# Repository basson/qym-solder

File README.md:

# qym-solder
QymSolder - Soldering station  three in one - hakko t12, hot air gun, d909/898D or analog.

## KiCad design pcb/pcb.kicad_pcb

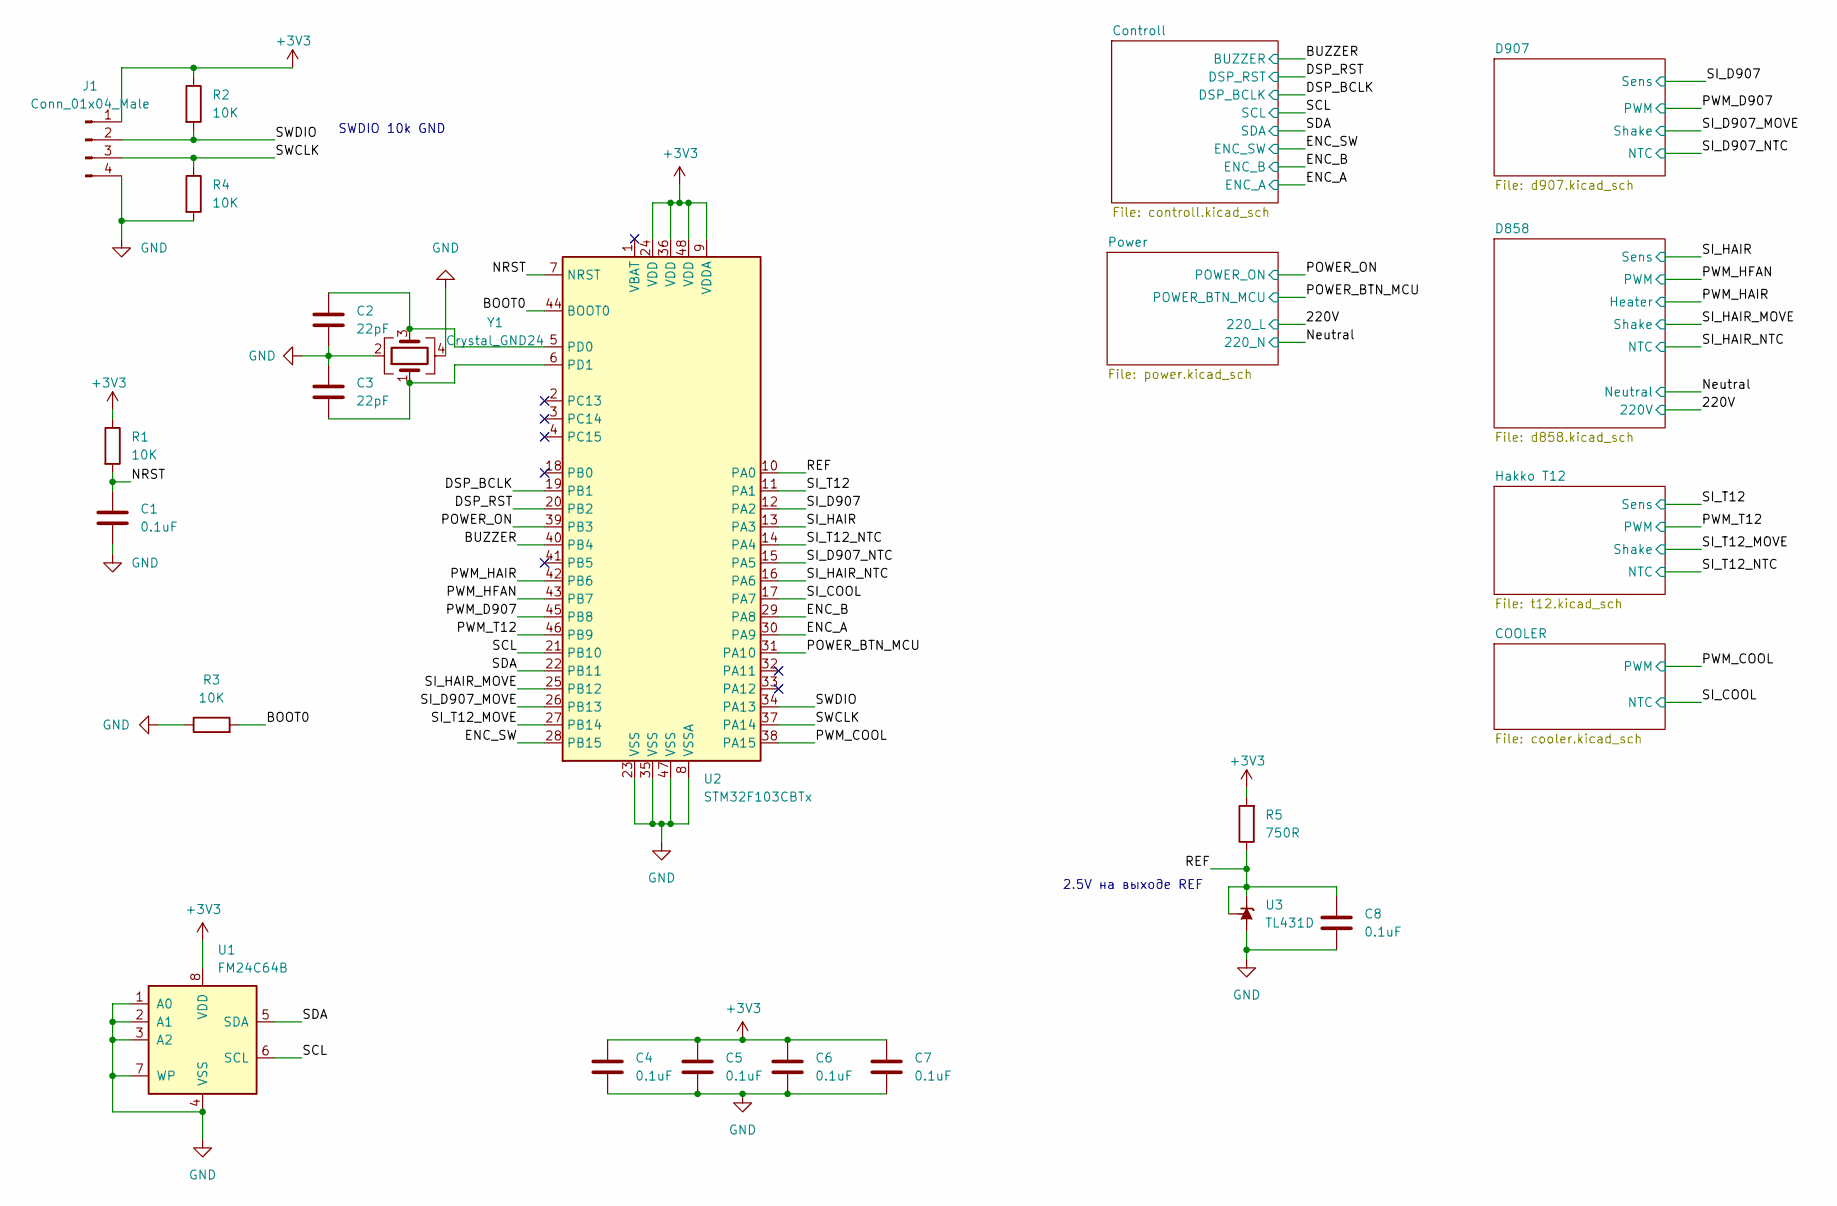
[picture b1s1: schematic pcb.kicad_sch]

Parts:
C1, C4, C5, C6, C7, C8: 0.1uF; C_1206_3216Metric_Pad1.33x1.80mm_HandSolder
C2, C3: 22pF; C_1206_3216Metric_Pad1.33x1.80mm_HandSolder
J1: Conn_01x04_Male; PinSocket_1x04_P2.54mm_Vertical
R1, R2, R3, R4: 10K; R_1206_3216Metric_Pad1.30x1.75mm_HandSolder
R5: 750R; R_1206_3216Metric_Pad1.30x1.75mm_HandSolder
U1: FM24C64B; SOIC-8_3.9x4.9mm_P1.27mm
U2: STM32F103CBTx; LQFP-48_7x7mm_P0.5mm
U3: TL431D; SOIC-8_3.9x4.9mm_P1.27mm
Y1: Crystal_GND24; Crystal_SMD_5032-4Pin_5.0x3.2mm

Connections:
+3V3: C4.1, C5.1, C6.1, C7.1, J1.1, R1.1, R2.1, R5.2, U1.8 (VDD), U2.9 (VDDA), U2.24 (VDD), U2.36 (VDD), U2.48 (VDD); also elsewhere on the board
/BOOT0: R3.2, U2.44 (BOOT0)
/BUZZER: U2.40 (PB4); also elsewhere on the board
/DSP_BCLK: U2.19 (PB1); also elsewhere on the board
/DSP_RST: U2.20 (PB2); also elsewhere on the board
/ENC_A: U2.30 (PA9); also elsewhere on the board
/ENC_B: U2.29 (PA8); also elsewhere on the board
/ENC_SW: U2.28 (PB15); also elsewhere on the board
/NRST: C1.2, R1.2, U2.7 (NRST)
/POWER_BTN_MCU: U2.31 (PA10); also elsewhere on the board
/POWER_ON: U2.39 (PB3); also elsewhere on the board
/PWM_COOL: U2.38 (PA15); also elsewhere on the board
/PWM_D907: U2.45 (PB8); also elsewhere on the board
/PWM_HAIR: U2.42 (PB6); also elsewhere on the board
/PWM_HFAN: U2.43 (PB7); also elsewhere on the board
/PWM_T12: U2.46 (PB9); also elsewhere on the board
/REF: C8.1, R5.1, U2.10 (PA0), U3.1 (K), U3.8 (REF)
/SCL: U1.6 (SCL), U2.21 (PB10); also elsewhere on the board
/SDA: U1.5 (SDA), U2.22 (PB11); also elsewhere on the board
/SI_COOL: U2.17 (PA7); also elsewhere on the board
/SI_D907: U2.12 (PA2); also elsewhere on the board
/SI_D907_MOVE: U2.26 (PB13); also elsewhere on the board
/SI_D907_NTC: U2.15 (PA5); also elsewhere on the board
/SI_HAIR: U2.13 (PA3); also elsewhere on the board
/SI_HAIR_MOVE: U2.25 (PB12); also elsewhere on the board
/SI_HAIR_NTC: U2.16 (PA6); also elsewhere on the board
/SI_T12: U2.11 (PA1); also elsewhere on the board
/SI_T12_MOVE: U2.27 (PB14); also elsewhere on the board
/SI_T12_NTC: U2.14 (PA4); also elsewhere on the board
/SWCLK: J1.3, R4.1, U2.37 (PA14)
/SWDIO: J1.2, R2.2, U2.34 (PA13)
GND: C1.1, C2.1, C3.2, C4.2, C5.2, C6.2, C7.2, C8.2, J1.4, R3.1, R4.2, U1.1 (A0), U1.2 (A1), U1.3 (A2), U1.4 (VSS), U1.7 (WP), U2.8 (VSSA), U2.23 (VSS), U2.35 (VSS), U2.47 (VSS), U3.2 (A), U3.3 (A), U3.6 (A), U3.7 (A), Y1.2, Y1.4; also elsewhere on the board
unnamed: C2.2, U2.5 (PD0), Y1.3
unnamed: C3.1, U2.6 (PD1), Y1.1

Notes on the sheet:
2.5V на выходе REF
SWDIO 10k GND

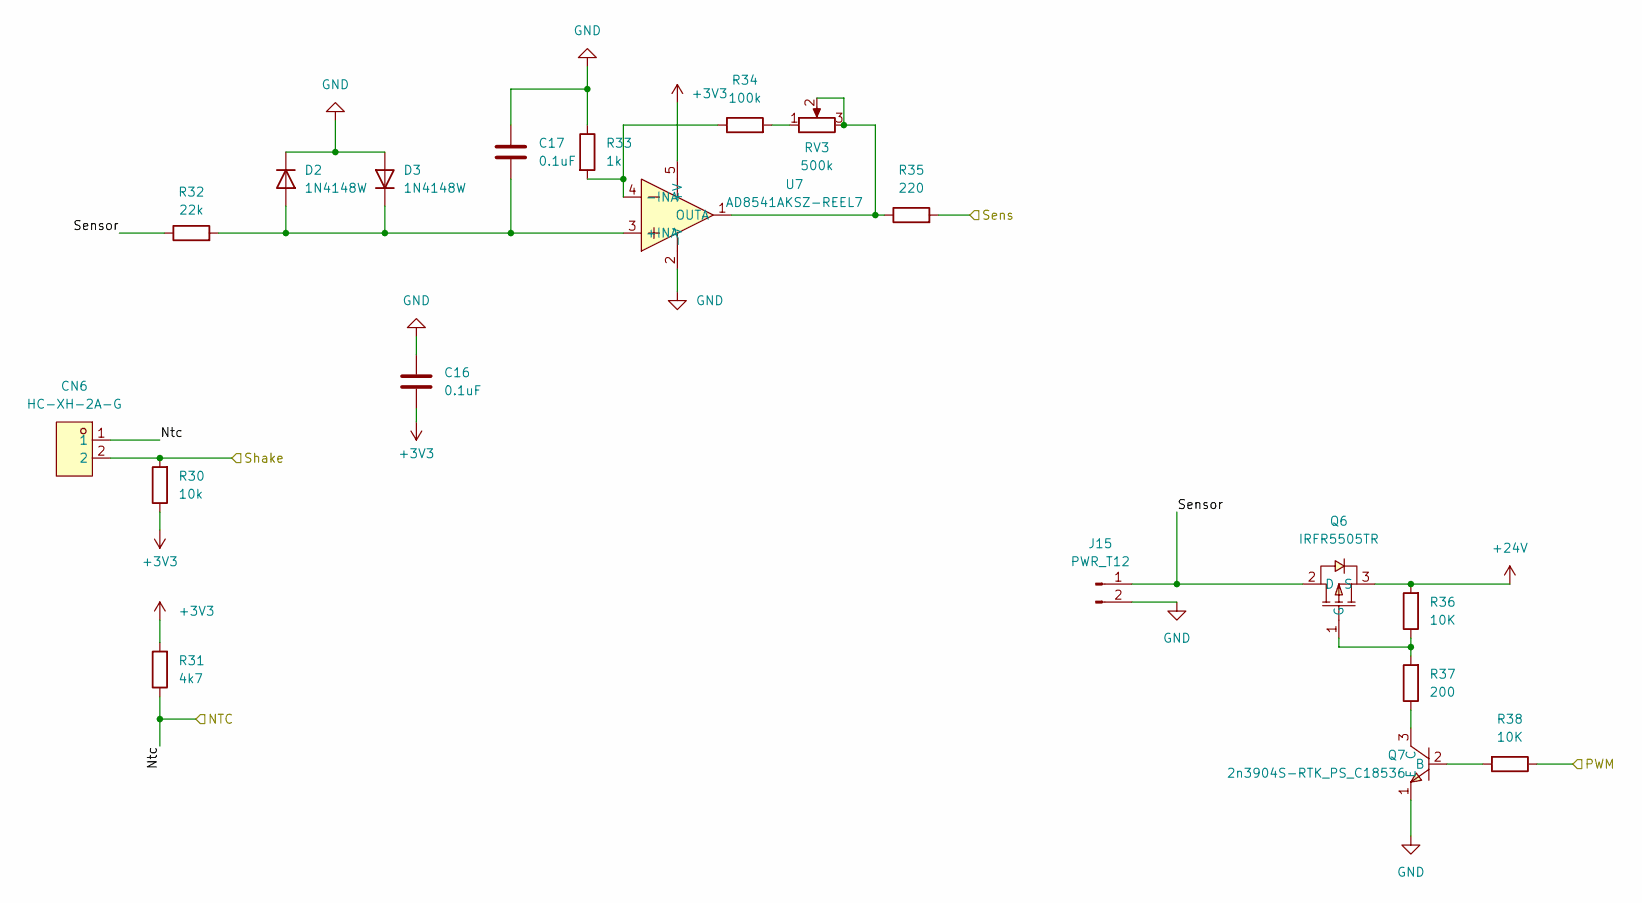
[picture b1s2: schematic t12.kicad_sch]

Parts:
C16, C17: 0.1uF; C_1206_3216Metric_Pad1.33x1.80mm_HandSolder
CN6: HC-XH-2A-G; CONN-TH_2P-P2.50_HC-XH-2A-G; LCSC Part C5341201
D2, D3: 1N4148W; D_SOD-123
J15: PWR_T12; TerminalBlock_Phoenix_MKDS-1,5-2_1x02_P5.00mm_Horizontal
Q6: IRFR5505TR; TO-252-3_L6.5-W5.8-P4.58-BR; LCSC Part C725084
Q7: 2n3904S-RTK_PS_C18536; SOT-23-3_L2.9-W1.3-P1.90-LS2.4-TR; LCSC Part C18536
R30: 10k; R_1206_3216Metric_Pad1.30x1.75mm_HandSolder
R31: 4k7; R_1206_3216Metric_Pad1.30x1.75mm_HandSolder
R32: 22k; R_1206_3216Metric_Pad1.30x1.75mm_HandSolder
R33: 1k; R_1206_3216Metric_Pad1.30x1.75mm_HandSolder
R34: 100k; R_1206_3216Metric_Pad1.30x1.75mm_HandSolder
R35: 220; R_1206_3216Metric_Pad1.30x1.75mm_HandSolder
R36, R38: 10K; R_1206_3216Metric_Pad1.30x1.75mm_HandSolder
R37: 200; R_1206_3216Metric_Pad1.30x1.75mm_HandSolder
RV3: 500k; Potentiometer_Bourns_3296W_Vertical
U7: AD8541AKSZ-REEL7; SOT-23-5; LCSC Part C143907

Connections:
+3V3: C16.2, R30.1, R31.2, U7.5 (+V); also elsewhere on the board
+24V: Q6.3 (S), R36.2; also elsewhere on the board
/Hakko T12/Sensor: J15.1, Q6.2 (D), R32.1
/PWM_T12: R38.1; also elsewhere on the board
/SI_T12: R35.2; also elsewhere on the board
/SI_T12_MOVE: CN6.2, R30.2; also elsewhere on the board
/SI_T12_NTC: CN6.1, R31.1; also elsewhere on the board
GND: C16.1, C17.1, D2.1 (K), D3.2 (A), J15.2, Q7.1 (E), R33.1, U7.2 (-V); also elsewhere on the board
unnamed: C17.2, D2.2 (A), D3.1 (K), R32.2, U7.3 (+INA)
unnamed: Q6.1 (G), R36.1, R37.2
unnamed: Q7.2 (B), R38.2
unnamed: Q7.3 (C), R37.1
unnamed: R34.2, RV3.1
unnamed: R33.2, R34.1, U7.4 (-INA)
unnamed: R35.1, RV3.2, RV3.3, U7.1 (OUTA)

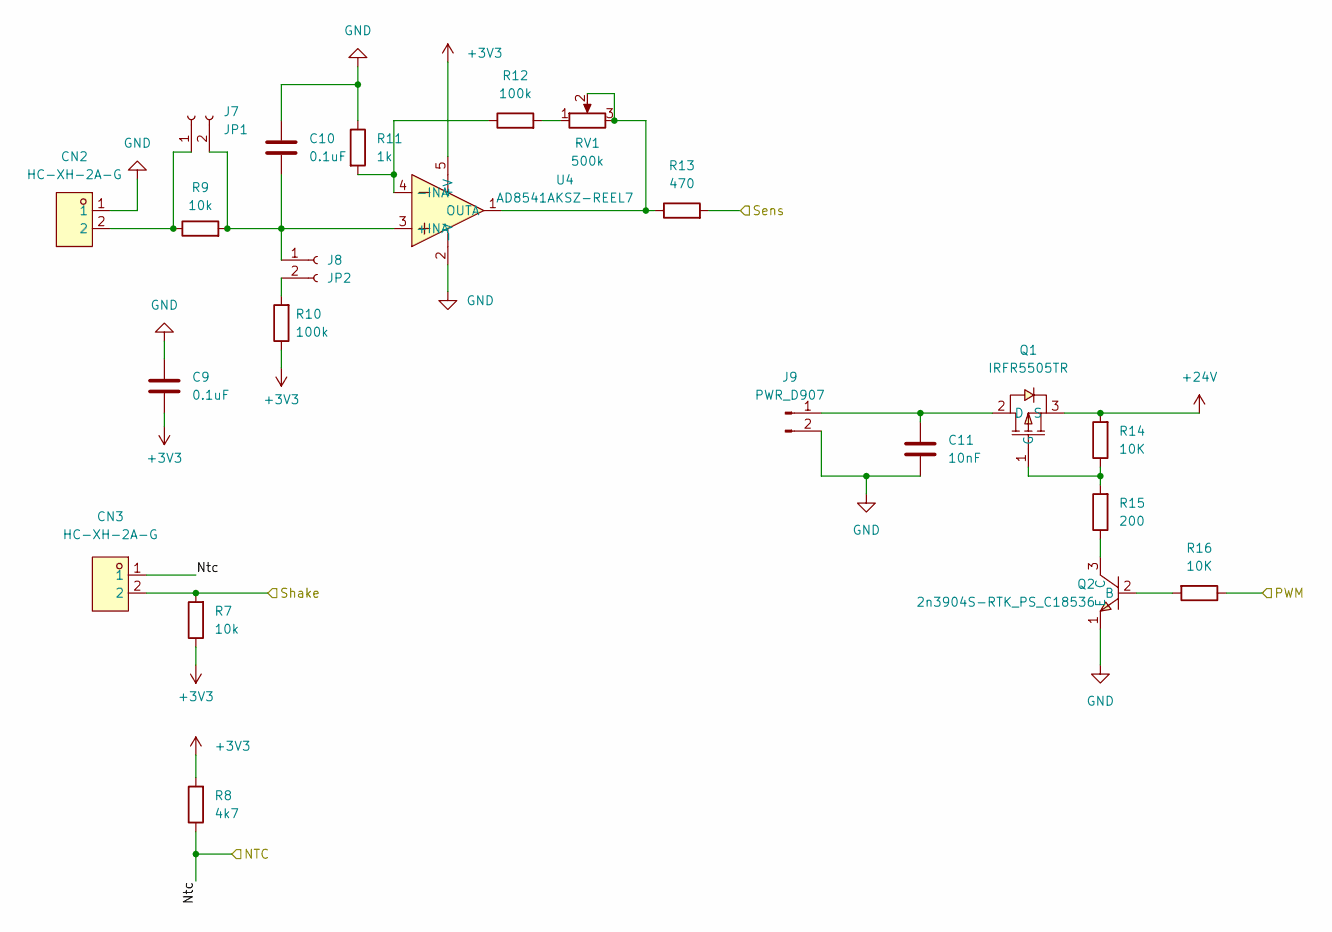
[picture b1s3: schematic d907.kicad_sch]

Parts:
C9, C10: 0.1uF; C_1206_3216Metric_Pad1.33x1.80mm_HandSolder
C11: 10nF; C_1206_3216Metric_Pad1.33x1.80mm_HandSolder
CN2, CN3: HC-XH-2A-G; CONN-TH_2P-P2.50_HC-XH-2A-G; LCSC Part C5341201
J7: JP1; PinSocket_1x02_P2.54mm_Vertical
J8: JP2; PinSocket_1x02_P2.54mm_Vertical
J9: PWR_D907; TerminalBlock_Phoenix_MKDS-1,5-2_1x02_P5.00mm_Horizontal
Q1: IRFR5505TR; TO-252-3_L6.5-W5.8-P4.58-BR; LCSC Part C725084
Q2: 2n3904S-RTK_PS_C18536; SOT-23-3_L2.9-W1.3-P1.90-LS2.4-TR; LCSC Part C18536
R7, R9: 10k; R_1206_3216Metric_Pad1.30x1.75mm_HandSolder
R8: 4k7; R_1206_3216Metric_Pad1.30x1.75mm_HandSolder
R10, R12: 100k; R_1206_3216Metric_Pad1.30x1.75mm_HandSolder
R11: 1k; R_1206_3216Metric_Pad1.30x1.75mm_HandSolder
R13: 470; R_1206_3216Metric_Pad1.30x1.75mm_HandSolder
R14, R16: 10K; R_1206_3216Metric_Pad1.30x1.75mm_HandSolder
R15: 200; R_1206_3216Metric_Pad1.30x1.75mm_HandSolder
RV1: 500k; Potentiometer_Bourns_3296W_Vertical
U4: AD8541AKSZ-REEL7; SOT-23-5; LCSC Part C143907

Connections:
+3V3: C9.2, R7.1, R8.2, R10.1, U4.5 (+V); also elsewhere on the board
+24V: Q1.3 (S), R14.2; also elsewhere on the board
/PWM_D907: R16.1; also elsewhere on the board
/SI_D907: R13.2; also elsewhere on the board
/SI_D907_MOVE: CN3.2, R7.2; also elsewhere on the board
/SI_D907_NTC: CN3.1, R8.1; also elsewhere on the board
GND: C9.1, C10.1, C11.1, CN2.1, J9.2, Q2.1 (E), R11.1, U4.2 (-V); also elsewhere on the board
unnamed: CN2.2, J7.1, R9.1
unnamed: C10.2, J7.2, J8.1, R9.2, U4.3 (+INA)
unnamed: J8.2, R10.2
unnamed: C11.2, J9.1, Q1.2 (D)
unnamed: Q1.1 (G), R14.1, R15.2
unnamed: Q2.2 (B), R16.2
unnamed: Q2.3 (C), R15.1
unnamed: R12.2, RV1.1
unnamed: R11.2, R12.1, U4.4 (-INA)
unnamed: R13.1, RV1.2, RV1.3, U4.1 (OUTA)

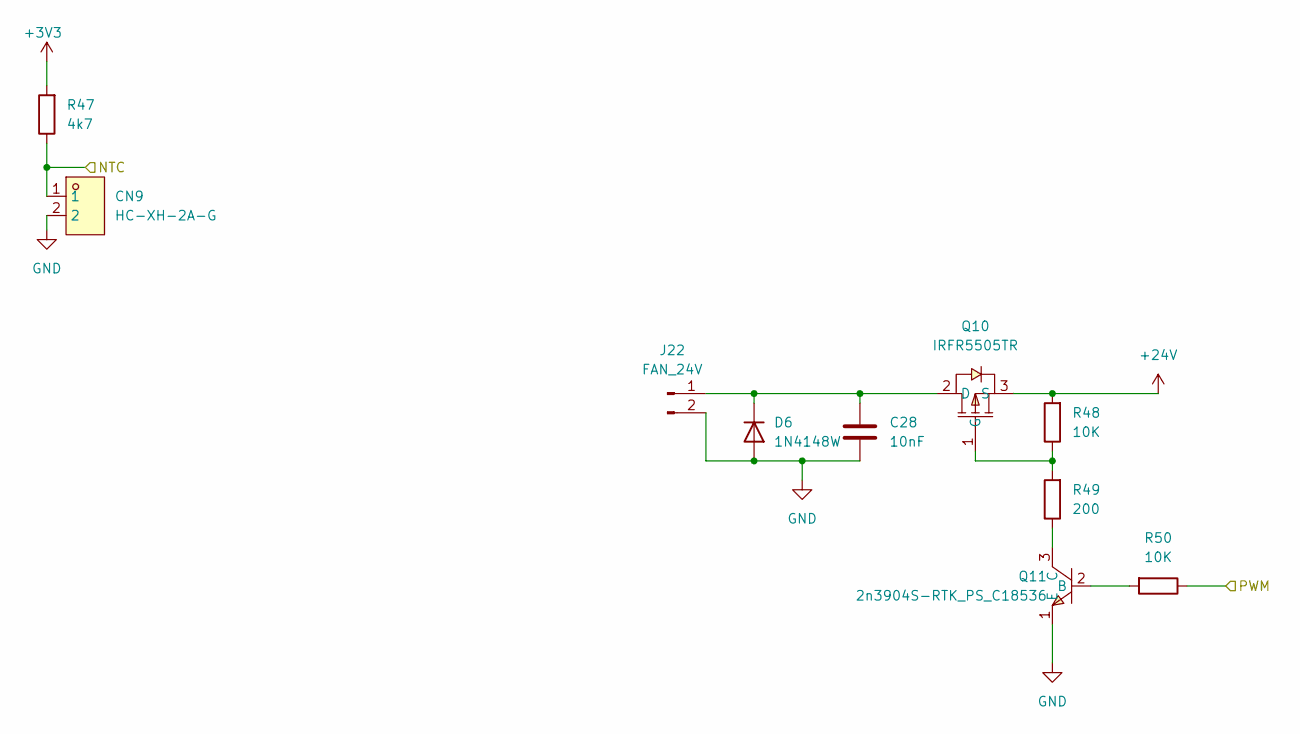
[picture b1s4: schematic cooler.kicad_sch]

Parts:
C28: 10nF; C_1206_3216Metric_Pad1.33x1.80mm_HandSolder
CN9: HC-XH-2A-G; CONN-TH_2P-P2.50_HC-XH-2A-G; LCSC Part C5341201
D6: 1N4148W; D_SOD-123
J22: FAN_24V; TerminalBlock_Phoenix_MKDS-1,5-2_1x02_P5.00mm_Horizontal
Q10: IRFR5505TR; TO-252-3_L6.5-W5.8-P4.58-BR; LCSC Part C725084
Q11: 2n3904S-RTK_PS_C18536; SOT-23-3_L2.9-W1.3-P1.90-LS2.4-TR; LCSC Part C18536
R47: 4k7; R_1206_3216Metric_Pad1.30x1.75mm_HandSolder
R48, R50: 10K; R_1206_3216Metric_Pad1.30x1.75mm_HandSolder
R49: 200; R_1206_3216Metric_Pad1.30x1.75mm_HandSolder

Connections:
+3V3: R47.2; also elsewhere on the board
+24V: Q10.3 (S), R48.2; also elsewhere on the board
/PWM_COOL: R50.1; also elsewhere on the board
/SI_COOL: CN9.1, R47.1; also elsewhere on the board
GND: C28.1, CN9.2, D6.2 (A), J22.2, Q11.1 (E); also elsewhere on the board
unnamed: C28.2, D6.1 (K), J22.1, Q10.2 (D)
unnamed: Q10.1 (G), R48.1, R49.2
unnamed: Q11.2 (B), R50.2
unnamed: Q11.3 (C), R49.1

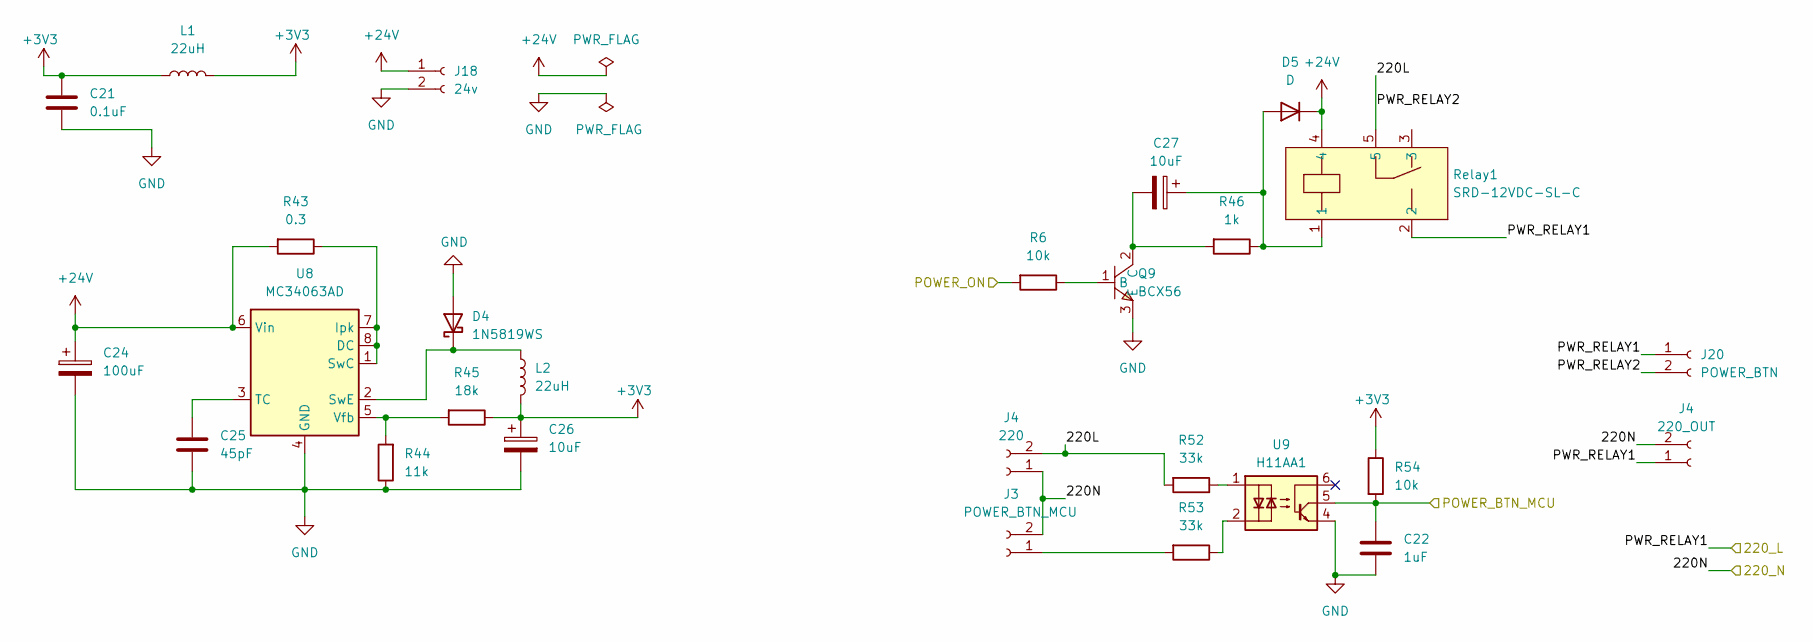
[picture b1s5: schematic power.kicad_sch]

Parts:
C21: 0.1uF; C_1206_3216Metric_Pad1.33x1.80mm_HandSolder
C22: 1uF; C_1206_3216Metric_Pad1.33x1.80mm_HandSolder
C24: 100uF; CP_Radial_D8.0mm_P3.80mm
C25: 45pF; C_1206_3216Metric_Pad1.33x1.80mm_HandSolder
C26, C27: 10uF; CP_Radial_D5.0mm_P2.50mm
D4: 1N5819WS; D_2114_3652Metric_Pad1.85x3.75mm_HandSolder
D5: D; D_SMA_Handsoldering
J3: POWER_BTN_MCU; TerminalBlock_Phoenix_MKDS-1,5-2_1x02_P5.00mm_Horizontal
J4: 220; TerminalBlock_Phoenix_MKDS-1,5-2_1x02_P5.00mm_Horizontal
J18: 24v; TerminalBlock_Phoenix_MKDS-1,5-2_1x02_P5.00mm_Horizontal
J20: POWER_BTN; TerminalBlock_Phoenix_MKDS-1,5-2_1x02_P5.00mm_Horizontal
L1: 22uH; L_1206_3216Metric_Pad1.22x1.90mm_HandSolder
L2: 22uH; L_6.3x6.3_H3
Q9: BCX56; SOT-89-3_L4.5-W2.5-P1.50-LS4.2-BR; LCSC Part C24280
R6, R54: 10k; R_1206_3216Metric_Pad1.30x1.75mm_HandSolder
R43: 0.3; R_1206_3216Metric_Pad1.30x1.75mm_HandSolder
R44: 11k; R_1206_3216Metric_Pad1.30x1.75mm_HandSolder
R45: 18k; R_1206_3216Metric_Pad1.30x1.75mm_HandSolder
R46: 1k; R_1206_3216Metric_Pad1.30x1.75mm_HandSolder
R52, R53: 33k; R_2512_6332Metric_Pad1.40x3.35mm_HandSolder
Relay1: SRD-12VDC-SL-C; RELAY-TH_SRD-XXVDC-XL-C; LCSC Part C30431
U8: MC34063AD; SOIC-8_3.9x4.9mm_P1.27mm
U9: H11AA1; DIP-6_W7.62mm_SMDSocket_SmallPads

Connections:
+3V3: C21.1, C26.1, L1.1, L1.2, L2.2, R45.1, R54.1; also elsewhere on the board
+24V: C24.1, D5.1 (K), J18.1, R43.2, Relay1.4, U8.6 (Vin); also elsewhere on the board
/POWER_BTN_MCU: C22.1, R54.2, U9.5; also elsewhere on the board
/POWER_ON: R6.2; also elsewhere on the board
GND: C21.2, C22.2, C24.2, C25.2, C26.2, D4.2 (A), J18.2, Q9.3 (E), R44.1, U8.4 (GND), U9.4; also elsewhere on the board
unnamed: D4.1 (K), L2.1, U8.2 (SwE)
unnamed: C27.1, D5.2 (A), R46.1, Relay1.1
unnamed: J3.1, R53.2
unnamed: Q9.1 (B), R6.1
unnamed: C27.2, Q9.2 (C), R46.2
unnamed: R52.1, U9.1
unnamed: R53.1, U9.2
unnamed: R43.1, U8.1 (SwC), U8.7 (Ipk), U8.8 (DC)
unnamed: C25.1, U8.3 (TC)
unnamed: R44.2, R45.2, U8.5 (Vfb)

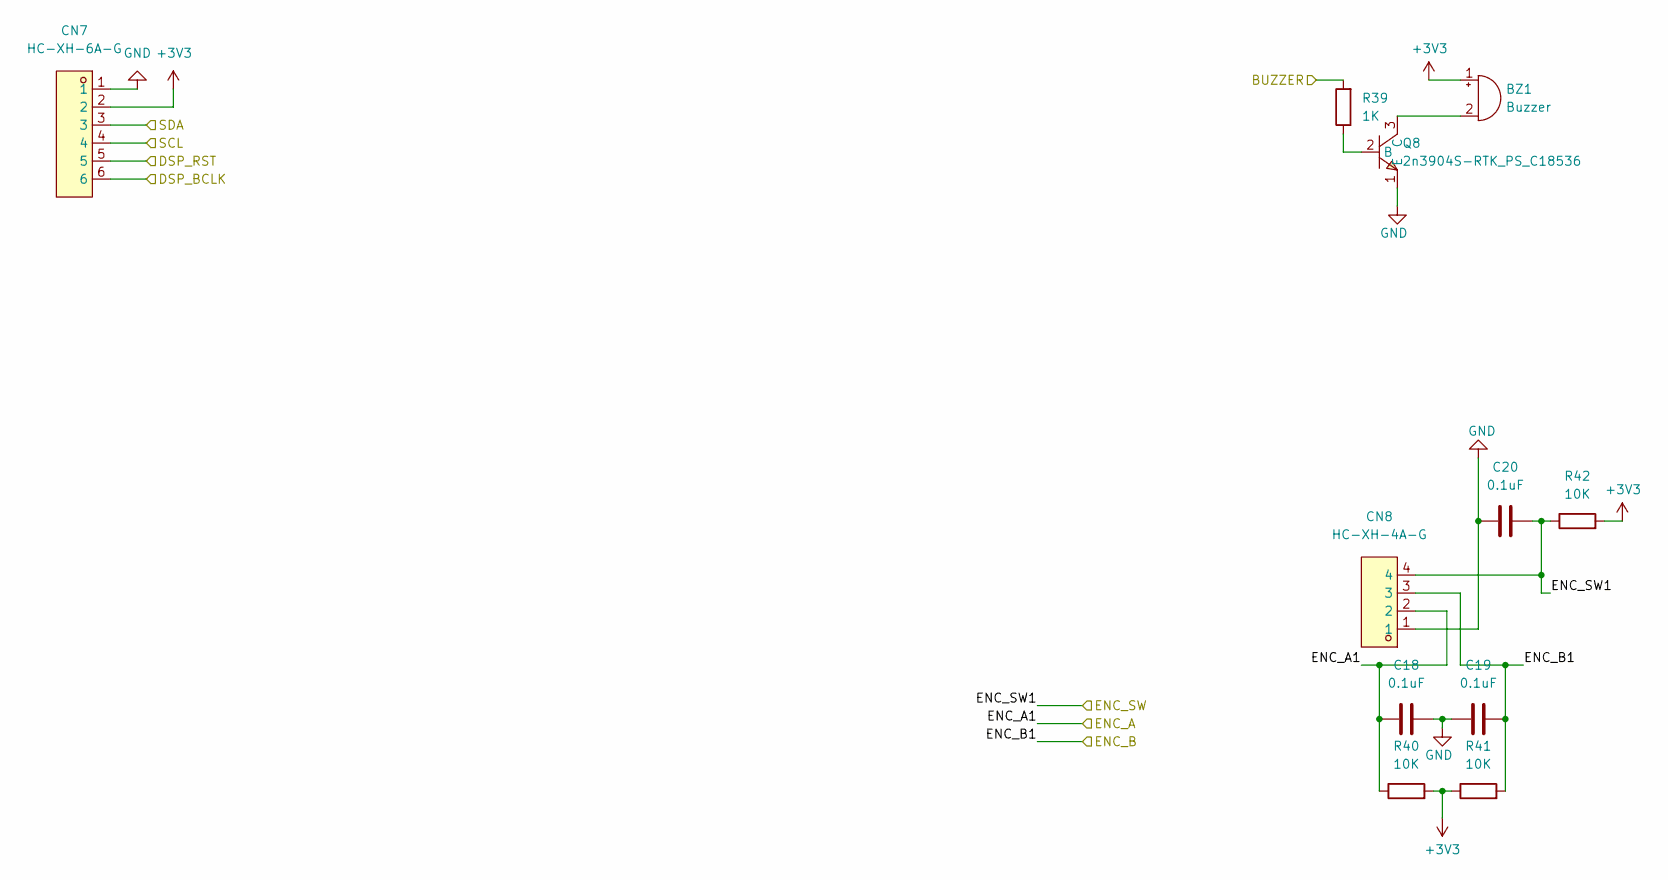
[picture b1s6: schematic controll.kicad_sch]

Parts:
BZ1: Buzzer; Buzzer_12x9.5RM7.6
C18, C19, C20: 0.1uF; C_1206_3216Metric_Pad1.33x1.80mm_HandSolder
CN7: HC-XH-6A-G; CONN-TH_6P-P2.50_HC-XH-6A-G; LCSC Part C5341205
CN8: HC-XH-4A-G; CONN-TH_4P-P2.50_HC-XH-4A-G; LCSC Part C5341203
Q8: 2n3904S-RTK_PS_C18536; SOT-23-3_L2.9-W1.3-P1.90-LS2.4-TR; LCSC Part C18536
R39: 1K; R_1206_3216Metric_Pad1.30x1.75mm_HandSolder
R40, R41, R42: 10K; R_1206_3216Metric_Pad1.30x1.75mm_HandSolder

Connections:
+3V3: BZ1.1 (-), CN7.2, R40.2, R41.1, R42.2; also elsewhere on the board
/BUZZER: R39.2; also elsewhere on the board
/DSP_BCLK: CN7.6; also elsewhere on the board
/DSP_RST: CN7.5; also elsewhere on the board
/ENC_A: C18.1, CN8.2, R40.1; also elsewhere on the board
/ENC_B: C19.2, CN8.3, R41.2; also elsewhere on the board
/ENC_SW: C20.1, CN8.4, R42.1; also elsewhere on the board
/SCL: CN7.4; also elsewhere on the board
/SDA: CN7.3; also elsewhere on the board
GND: C18.2, C19.1, C20.2, CN7.1, CN8.1, Q8.1 (E); also elsewhere on the board
unnamed: BZ1.2 (+), Q8.3 (C)
unnamed: Q8.2 (B), R39.1

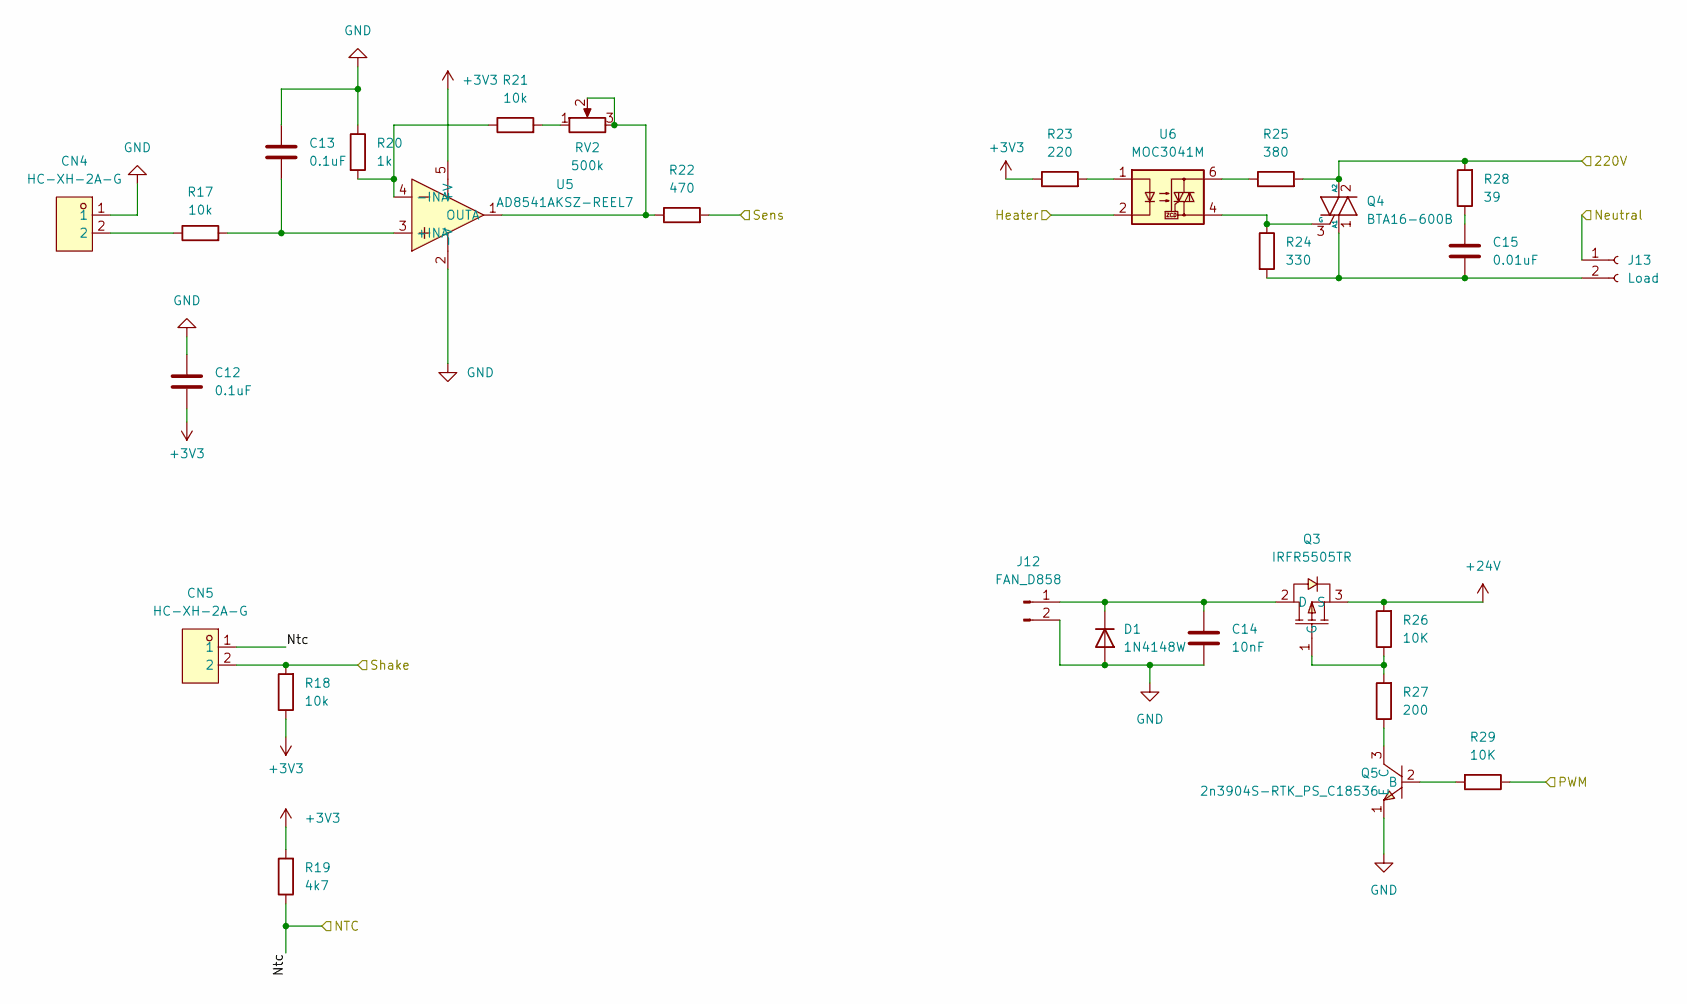
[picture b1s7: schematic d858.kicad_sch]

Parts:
C12, C13: 0.1uF; C_1206_3216Metric_Pad1.33x1.80mm_HandSolder
C14: 10nF; C_1206_3216Metric_Pad1.33x1.80mm_HandSolder
C15: 0.01uF; C_Disc_D11.0mm_W5.0mm_P5.00mm
CN4, CN5: HC-XH-2A-G; CONN-TH_2P-P2.50_HC-XH-2A-G; LCSC Part C5341201
D1: 1N4148W; D_SOD-123
J12: FAN_D858; TerminalBlock_Phoenix_MKDS-1,5-2_1x02_P5.00mm_Horizontal
J13: Load; TerminalBlock_Phoenix_MKDS-1,5-2_1x02_P5.00mm_Horizontal
Q3: IRFR5505TR; TO-252-3_L6.5-W5.8-P4.58-BR; LCSC Part C725084
Q4: BTA16-600B; TO-220-3_Vertical
Q5: 2n3904S-RTK_PS_C18536; SOT-23-3_L2.9-W1.3-P1.90-LS2.4-TR; LCSC Part C18536
R17, R18, R21: 10k; R_1206_3216Metric_Pad1.30x1.75mm_HandSolder
R19: 4k7; R_1206_3216Metric_Pad1.30x1.75mm_HandSolder
R20: 1k; R_1206_3216Metric_Pad1.30x1.75mm_HandSolder
R22: 470; R_1206_3216Metric_Pad1.30x1.75mm_HandSolder
R23: 220; R_1206_3216Metric_Pad1.30x1.75mm_HandSolder
R24: 330; R_2512_6332Metric_Pad1.40x3.35mm_HandSolder
R25: 380; R_2512_6332Metric_Pad1.40x3.35mm_HandSolder
R26, R29: 10K; R_1206_3216Metric_Pad1.30x1.75mm_HandSolder
R27: 200; R_1206_3216Metric_Pad1.30x1.75mm_HandSolder
R28: 39; R_2512_6332Metric_Pad1.40x3.35mm_HandSolder
RV2: 500k; Potentiometer_Bourns_3296W_Vertical
U5: AD8541AKSZ-REEL7; SOT-23-5; LCSC Part C143907
U6: MOC3041M; DIP-6_W7.62mm_LongPads

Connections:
+3V3: C12.2, R18.1, R19.2, R23.1, U5.5 (+V); also elsewhere on the board
+24V: Q3.3 (S), R26.2; also elsewhere on the board
/PWM_HAIR: U6.2; also elsewhere on the board
/PWM_HFAN: R29.1; also elsewhere on the board
/SI_HAIR: R22.2; also elsewhere on the board
/SI_HAIR_MOVE: CN5.2, R18.2; also elsewhere on the board
/SI_HAIR_NTC: CN5.1, R19.1; also elsewhere on the board
GND: C12.1, C13.1, C14.1, CN4.1, D1.2 (A), J12.2, Q5.1 (E), R20.1, U5.2 (-V); also elsewhere on the board
unnamed: C15.1, R28.1
unnamed: CN4.2, R17.1
unnamed: C14.2, D1.1 (K), J12.1, Q3.2 (D)
unnamed: C15.2, J13.2, Q4.1 (A1), R24.2
unnamed: Q3.1 (G), R26.1, R27.2
unnamed: Q4.3 (G), R24.1, U6.4
unnamed: Q5.2 (B), R29.2
unnamed: Q5.3 (C), R27.1
unnamed: R21.2, RV2.1
unnamed: R23.2, U6.1
unnamed: R25.1, U6.6
unnamed: C13.2, R17.2, U5.3 (+INA)
unnamed: R20.2, R21.1, U5.4 (-INA)
unnamed: R22.1, RV2.2, RV2.3, U5.1 (OUTA)

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
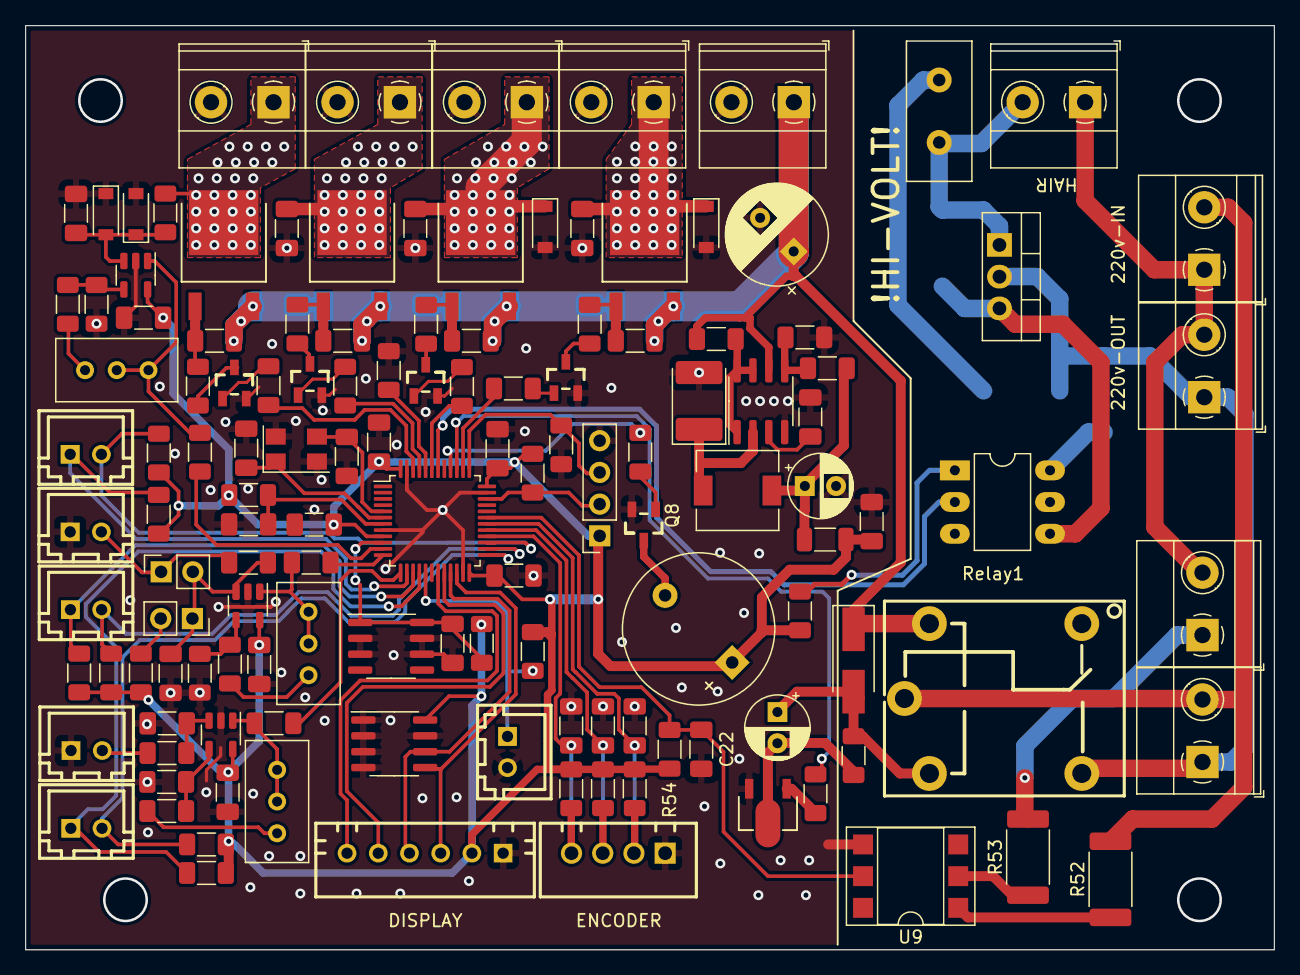
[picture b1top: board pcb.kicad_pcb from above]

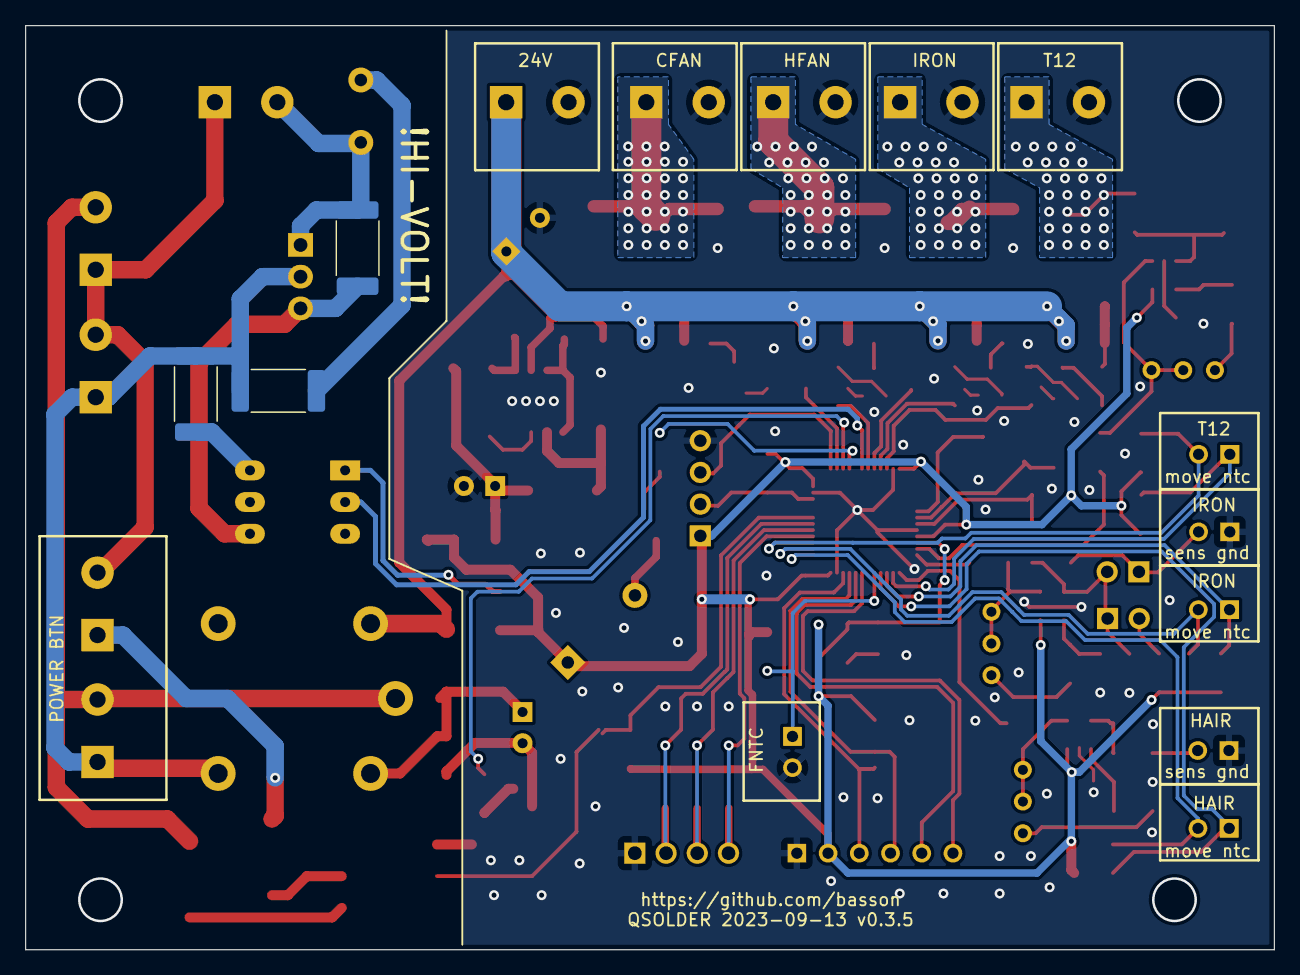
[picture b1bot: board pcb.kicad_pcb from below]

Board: 2 copper layers, 100.0 x 74.0 mm, 135 parts (3 on the bottom side), 86 nets.

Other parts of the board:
J2: 220; TerminalBlock_Phoenix_MKDS-1,5-2_1x02_P5.00mm_Horizontal

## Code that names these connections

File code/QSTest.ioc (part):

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Mcu.Name=STM32F103C(8-B)Tx
Mcu.Package=LQFP48
Mcu.UserName=STM32F103CBTx
PA0-WKUP.GPIOParameters=GPIO_Label
PA0-WKUP.GPIO_Label=REF
PA0-WKUP.Signal=ADCx_IN0
PA1.GPIOParameters=GPIO_Label
PA1.GPIO_Label=SI_T12
PA1.Signal=ADCx_IN1
PA10.GPIOParameters=GPIO_Label,GPIO_ModeDefaultEXTI
PA10.GPIO_Label=POWER_BTN_MCU
PA10.GPIO_ModeDefaultEXTI=GPIO_MODE_IT_FALLING
PA10.Signal=GPXTI10
PA13.Mode=Serial_Wire
PA13.Signal=SYS_JTMS-SWDIO
PA14.Mode=Serial_Wire
PA14.Signal=SYS_JTCK-SWCLK
PA15.GPIOParameters=GPIO_Label
PA15.GPIO_Label=PWM_COOL
PA15.Signal=S_TIM2_CH1_ETR
PA2.GPIOParameters=GPIO_Label
PA2.GPIO_Label=SI_IRON
PA2.Signal=ADCx_IN2
PA3.GPIOParameters=GPIO_Label
PA3.GPIO_Label=SI_HAIR
PA3.Signal=ADCx_IN3
PA4.GPIOParameters=GPIO_Label
PA4.GPIO_Label=SI_T12_NTC
PA4.Signal=ADCx_IN4
PA5.GPIOParameters=GPIO_Label
PA5.GPIO_Label=SI_IRON_NTC
PA5.Signal=ADCx_IN5
PA6.GPIOParameters=GPIO_Label
PA6.GPIO_Label=SI_HAIR_NTC
PA6.Signal=ADCx_IN6
PA7.GPIOParameters=GPIO_Label
PA7.GPIO_Label=SI_COOL
PA7.Signal=ADCx_IN7
PA8.GPIOParameters=GPIO_Label
PA8.GPIO_Label=ENC_B
PA8.Signal=S_TIM1_CH1
PA9.GPIOParameters=GPIO_Label
PA9.GPIO_Label=ENC_A
PA9.Signal=S_TIM1_CH2
PB1.GPIOParameters=GPIO_Label
PB1.GPIO_Label=DSP_BCLK
PB1.Signal=GPIO_Output
PB10.GPIOParameters=GPIO_Label
PB10.GPIO_Label=SCL
PB10.Mode=I2C
PB10.Signal=I2C2_SCL
PB11.GPIOParameters=GPIO_Label
PB11.GPIO_Label=SDA
PB11.Mode=I2C
PB11.Signal=I2C2_SDA
PB12.GPIOParameters=GPIO_Label,GPIO_ModeDefaultEXTI
PB12.GPIO_Label=HAIR_MOVE
PB12.GPIO_ModeDefaultEXTI=GPIO_MODE_IT_FALLING
PB12.Signal=GPXTI12
PB13.GPIOParameters=GPIO_Label,GPIO_ModeDefaultEXTI
PB13.GPIO_Label=IRON_MOVE
PB13.GPIO_ModeDefaultEXTI=GPIO_MODE_IT_FALLING
PB13.Signal=GPXTI13
PB14.GPIOParameters=GPIO_PuPd,GPIO_Label,GPIO_ModeDefaultEXTI
PB14.GPIO_Label=T12_MOVE
PB14.GPIO_ModeDefaultEXTI=GPIO_MODE_IT_RISING
PB14.GPIO_PuPd=GPIO_NOPULL
PB14.Signal=GPXTI14
PB15.GPIOParameters=GPIO_Label,GPIO_ModeDefaultEXTI
PB15.GPIO_Label=ENC_SW
PB15.GPIO_ModeDefaultEXTI=GPIO_MODE_IT_FALLING
PB15.Signal=GPXTI15
PB2.GPIOParameters=GPIO_Label
PB2.GPIO_Label=DSP_RST
PB2.Signal=GPIO_Output
PB3.GPIOParameters=GPIO_Label
PB3.GPIO_Label=POWER_ON
PB3.Signal=GPIO_Output
PB4.GPIOParameters=GPIO_Speed,PinState,GPIO_PuPd,GPIO_Label
PB4.GPIO_Label=BUZZER
PB4.GPIO_PuPd=GPIO_PULLDOWN
PB4.GPIO_Speed=GPIO_SPEED_FREQ_MEDIUM
PB4.PinState=GPIO_PIN_RESET
PB4.Signal=GPIO_Output
PB6.GPIOParameters=GPIO_ModeDefaultPP,GPIO_Label
PB6.GPIO_Label=PWM_HAIR
PB6.GPIO_ModeDefaultPP=GPIO_MODE_AF_PP
PB6.Signal=S_TIM4_CH1
PB7.GPIOParameters=GPIO_Label
PB7.GPIO_Label=PWM_HFAN
PB7.Signal=S_TIM4_CH2
PB8.GPIOParameters=GPIO_Label
PB8.GPIO_Label=PWM_D907
PB8.Signal=S_TIM4_CH3
PB9.GPIOParameters=GPIO_Label
PB9.GPIO_Label=PWM_T12
PB9.Signal=S_TIM4_CH4
PD0-OSC_IN.Mode=HSE-External-Oscillator
PD0-OSC_IN.Signal=RCC_OSC_IN
PD1-OSC_OUT.Mode=HSE-External-Oscillator
PD1-OSC_OUT.Signal=RCC_OSC_OUT
RCC.SYSCLKFreq_VALUE=72000000
RCC.SYSCLKSource=RCC_SYSCLKSOURCE_PLLCLK
board=custom

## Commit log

2024-01-02 Update README.md
    Fix name repository
2024-01-06 First commit on all source
2024-01-06 Refract older namespaces
2024-01-06 Add submodules for lib folder
2024-01-06 Release base screens, and base functionan encoder and buttons.
2024-01-07 Small refract naming. Release screen static makeup on config T12, HAir Gun and Solder Hand. And release navigate for config menu.
2024-01-07 Add qymos:common library. Dev class controll all hands. add emem functioanal. See main streem on youtube! https://www.youtube.com/@basson_xvi/streams
2024-01-09 Release gui screen default config. some optimization.
2024-01-13 Нарисованы все иконки для меню в 8px Реализованы все всплывающие диалоги в меню настроек паяльных ручек. Сверстан экран для PidAutotune
2024-01-14 Tested app LCD Image Converter and fix IconFlow12px.h
2024-01-14 Update qymos-stm32-gui-monochrome
2024-01-18 Release default setting load and save on eeeprom.
2024-01-24 Добавили функционал включения выключения выбора температуры на табы (Хакко Т12, Простой паяльник). Добавили сон и работу паяльников и фена
2024-01-24 add back qymos-stm32-common library for submodules
2024-02-03 Add tabs on hot air gun functionality.
2024-02-04 Some refract library and add new library
2024-02-04 Refract fow new version gui-monochrome libs
2024-02-04 update ssd1306 drivers
2024-02-05 Use new class on library qymos-hui (buttonIrq)
2024-02-05 Change resistense on R46 to 1k (add raleay on more power)
2024-04-06 Fix Controll class (work corectly hot air gun and solders. and some fix
2024-04-07 Add Logo,Warging, Error icons. Add Startup screen and Shutdown.
2024-05-05 Fix string warning (const char array), and some warrnings.
